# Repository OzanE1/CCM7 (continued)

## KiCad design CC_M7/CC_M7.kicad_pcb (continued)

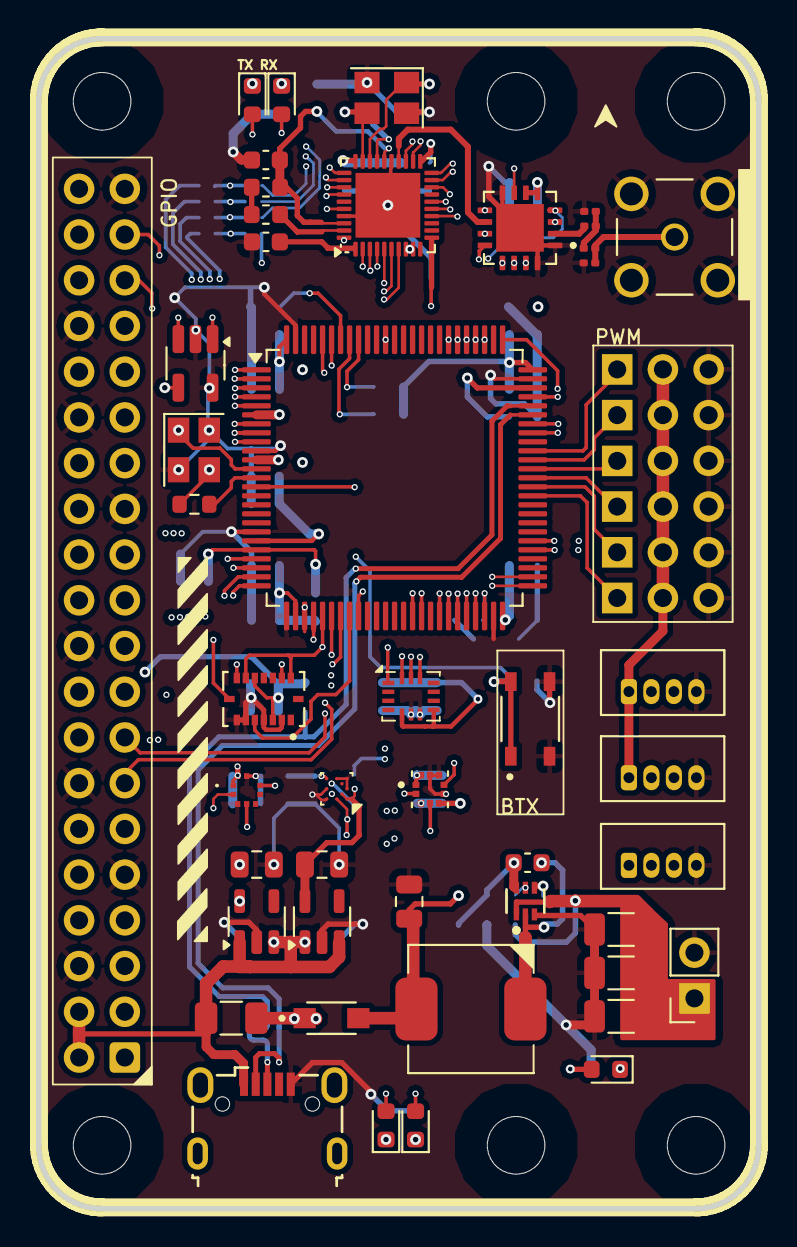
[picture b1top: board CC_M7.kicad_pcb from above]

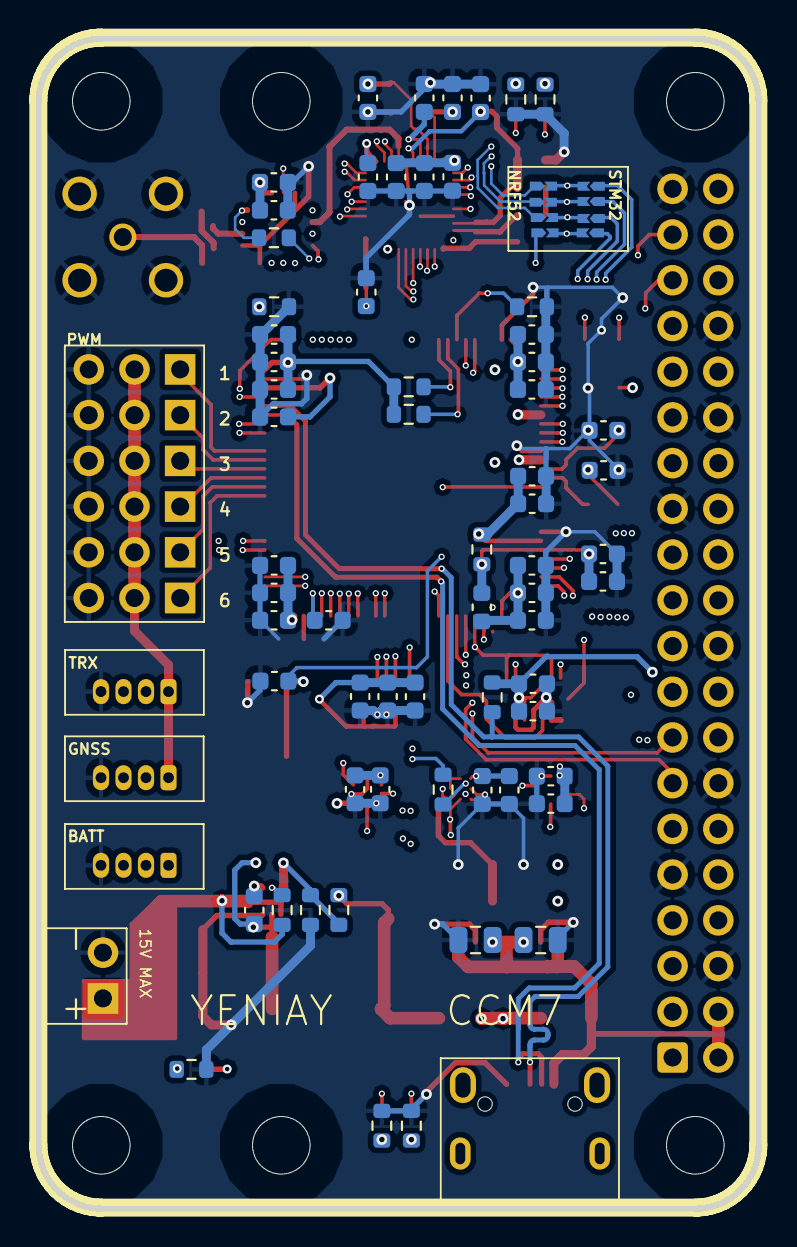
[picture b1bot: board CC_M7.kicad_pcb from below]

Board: 4 copper layers, 40.0 x 65.0 mm, 129 parts (63 on the bottom side), 110 nets.

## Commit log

2024-10-31 Modules added.
2024-10-31 Readme TEST
2024-10-31 Readme update
2024-11-19 BMP388 updated.
2024-11-19 BMM150 updated.
2024-11-22 BMI088 updated.
2024-12-03 ESP32-C3 Updated.
2024-12-06 test
2024-12-06 test2
2024-12-08 Voltage Regulator updated
2024-12-13 STM32H743VIT6 labels updated
2024-12-13 footprints
2024-12-13 update schematic
2024-12-14 nRF52820+nRf21540 add
2024-12-14 update rf scheme
2024-12-15 nRF52820 schematic update
2024-12-16 CCM7 nRF52820 Update
2024-12-17 nrf52820 draw
2024-12-17 VoltageR updated
2024-12-22 gitignore
2024-12-22 CCM7
2024-12-24 label control
2024-12-27 gitignore refactor
2024-12-27 Control board updated
2024-12-27 Connectors updated
2024-12-27 NRF pins updated
2024-12-27 EEPROM
2024-12-27 EEPROM merge
2024-12-29 final schematic 6 warning
2025-01-24 schematic control comment
2025-02-01 CCM7.docx Updated Connector redefinition | Power Read Update
2025-02-01 Changes updated @ CCM7.docx
2025-02-02 Footprint assignment 1/2
2025-02-08 IIM42652 schematic added
2025-02-08 New sensors
2025-02-08 BMP581 added schematic
2025-02-09 net classes added
2025-02-09 assigned footprint completed
2025-02-09 BMP581 and ICP20100 added
2025-02-12 ready to start PCB drawing
2025-02-13 nRF PCB placement completed
2025-02-18 Component placement completed
2025-02-18 Mounting Hole added.
2025-02-20 1x04 connectors chosen and added
2025-02-21 constraints set
2025-02-21 impadance control check and track thickness added
2025-02-22 Schematic pdf added.
2025-02-22 [200~
2025-02-22 Reverse current protection added.
2025-02-22 PCB track draw.
2025-02-23 Reverse current protection added. | Routing progress.
2025-02-23 Routing Progress | BMM150 removed.
2025-03-02 USB Pullup added, oscillator capacitors updated.
2025-03-08 Routing | Silkscreen Design Completed. | Power Led Added. | Schematic PDF deleted | Mounting Hole Pad Clearance added. | BMM150 Conneciton Fixed.
2025-03-10 Small vias replaced big vias
2025-03-31 error chekc
2025-04-01 Error check
2025-04-02 warning check
2025-04-02 Zones properties changed.
2025-04-05 Error and warning completed check.
2025-04-05 BOM added.
2025-04-20 Adding 3d models.
2025-04-21 3d models added.
